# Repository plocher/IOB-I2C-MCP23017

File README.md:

# IOB-I2C-MCP23017
## License: CERN Open Hardware Licence v1.2

IOB I2C MCP23017 based IO Expander

The MCP23017 expander is an inexpensive and reliable device that supports up to 8x instances on a single I2C chain.

### Specifications

Each board provides a latched set of 16x IO points, with each point
being software selectable to be either an input or an output. The
individual points are reasonably protected from the environment, and can
source or sink 20 mA each (25mA absolute max).

### Communication Protocol

```C++
    enum MCP23017Registers {
        MCP23017_IODIRA   = 0x00,
        MCP23017_IODIRB   = 0x01,
        MCP23017_IPOLA    = 0x02,
        MCP23017_IPOLB    = 0x03,
        MCP23017_GPINTENA = 0x04,
        MCP23017_GPINTENB = 0x05,
        MCP23017_DEFVALA  = 0x06,
        MCP23017_DEFVALB  = 0x07,
        MCP23017_INTCONA  = 0x08,
        MCP23017_INTCONB  = 0x09,
        MCP23017_IOCONA   = 0x0A,
        MCP23017_IOCONB   = 0x0B,
        MCP23017_GPPUA    = 0x0C,
        MCP23017_GPPUB    = 0x0D,
        MCP23017_INTFA    = 0x0E,
        MCP23017_INTFB    = 0x0F,
        MCP23017_INTCAPA  = 0x10,
        MCP23017_INTCAPB  = 0x11,
        MCP23017_GPIOA    = 0x12,
        MCP23017_GPIOB    = 0x13,
        MCP23017_OLATA    = 0x14,
        MCP23017_OLATB    = 0x15,
    };

void I2Cexpander::init23017(uint8_t i2caddr, uint16_t dir) {
    if (i2caddr < base23017) {
        _i2c_address = base23017 + i2caddr;
    } else {
        _i2c_address = i2caddr;
    }
    Wire.beginTransmission(_i2c_address);
    Wire.write(MCP23017_IODIRA);
    Wire.write(0xff & dir);         // Low byte
    Wire.endTransmission();

    Wire.beginTransmission(_i2c_address);
    Wire.write(MCP23017_IODIRB);
    Wire.write(0xff & (dir >> 8));  // High byte
    Wire.endTransmission();

    // enable 100k pullups on all inputs...
    Wire.beginTransmission(_i2c_address);
    Wire.write(MCP23017_GPPUA);
    Wire.write(0xff & dir);         // Low byte
    Wire.endTransmission();

    Wire.beginTransmission(_i2c_address);
    Wire.write(MCP23017_GPPUB);
    Wire.write(0xff & (dir >> 8));  // High byte
    Wire.endTransmission();
}

uint32_t I2Cexpander::read23017() {
    uint32_t data = 0;
    Wire.beginTransmission(_i2c_address);
    Wire.write(MCP23017_GPIOA);
    Wire.endTransmission();

    Wire.requestFrom(_i2c_address, (uint8_t)2, (uint8_t)1);
    data = Wire.read();
    data |= (Wire.read() << 8);
    return data;
}

void I2Cexpander::write23017(uint32_t data) {
    data = data | _config;
    Wire.beginTransmission(_i2c_address);
    Wire.write(MCP23017_GPIOA);
    Wire.write(0xff & data);  //  low byte
    Wire.write(data >> 8);    //  high byte
    Wire.endTransmission();
}
```

See [I2Cexpander-lib](/pages/I2Cexpander "wikilink") for a more complete interface
library.

### Addressing
The addres selection for the MCP23017 is simple - set the desired address (in binary) on the 3x address selection switches.

**AD2**|**AD1**|**AD0**|**A6**|**A5**|**A4**|**A3**|**A2**|**A1**|**A0**|**ADDRESS (HEX)**
:-----:|:-----:|:-----:|:-----:|:-----:|:-----:|:-----:|:-----:|:-----:|:-----:|:-----:
GND|GND|GND|0|1|0|0|0|0|0|0x20
GND|GND|V+|0|1|0|0|0|0|1|0x21
GND|V+|GND|0|1|0|0|0|1|0|0x22
GND|V+|V+|0|1|0|0|0|1|1|0x23
V+|GND|GND|0|1|0|0|1|0|0|0x24
V+|GND|V+|0|1|0|0|1|0|1|0x25
V+|V+|GND|0|1|0|0|1|1|0|0x26
V+|V+|V+|0|1|0|0|1|1|1|0x27

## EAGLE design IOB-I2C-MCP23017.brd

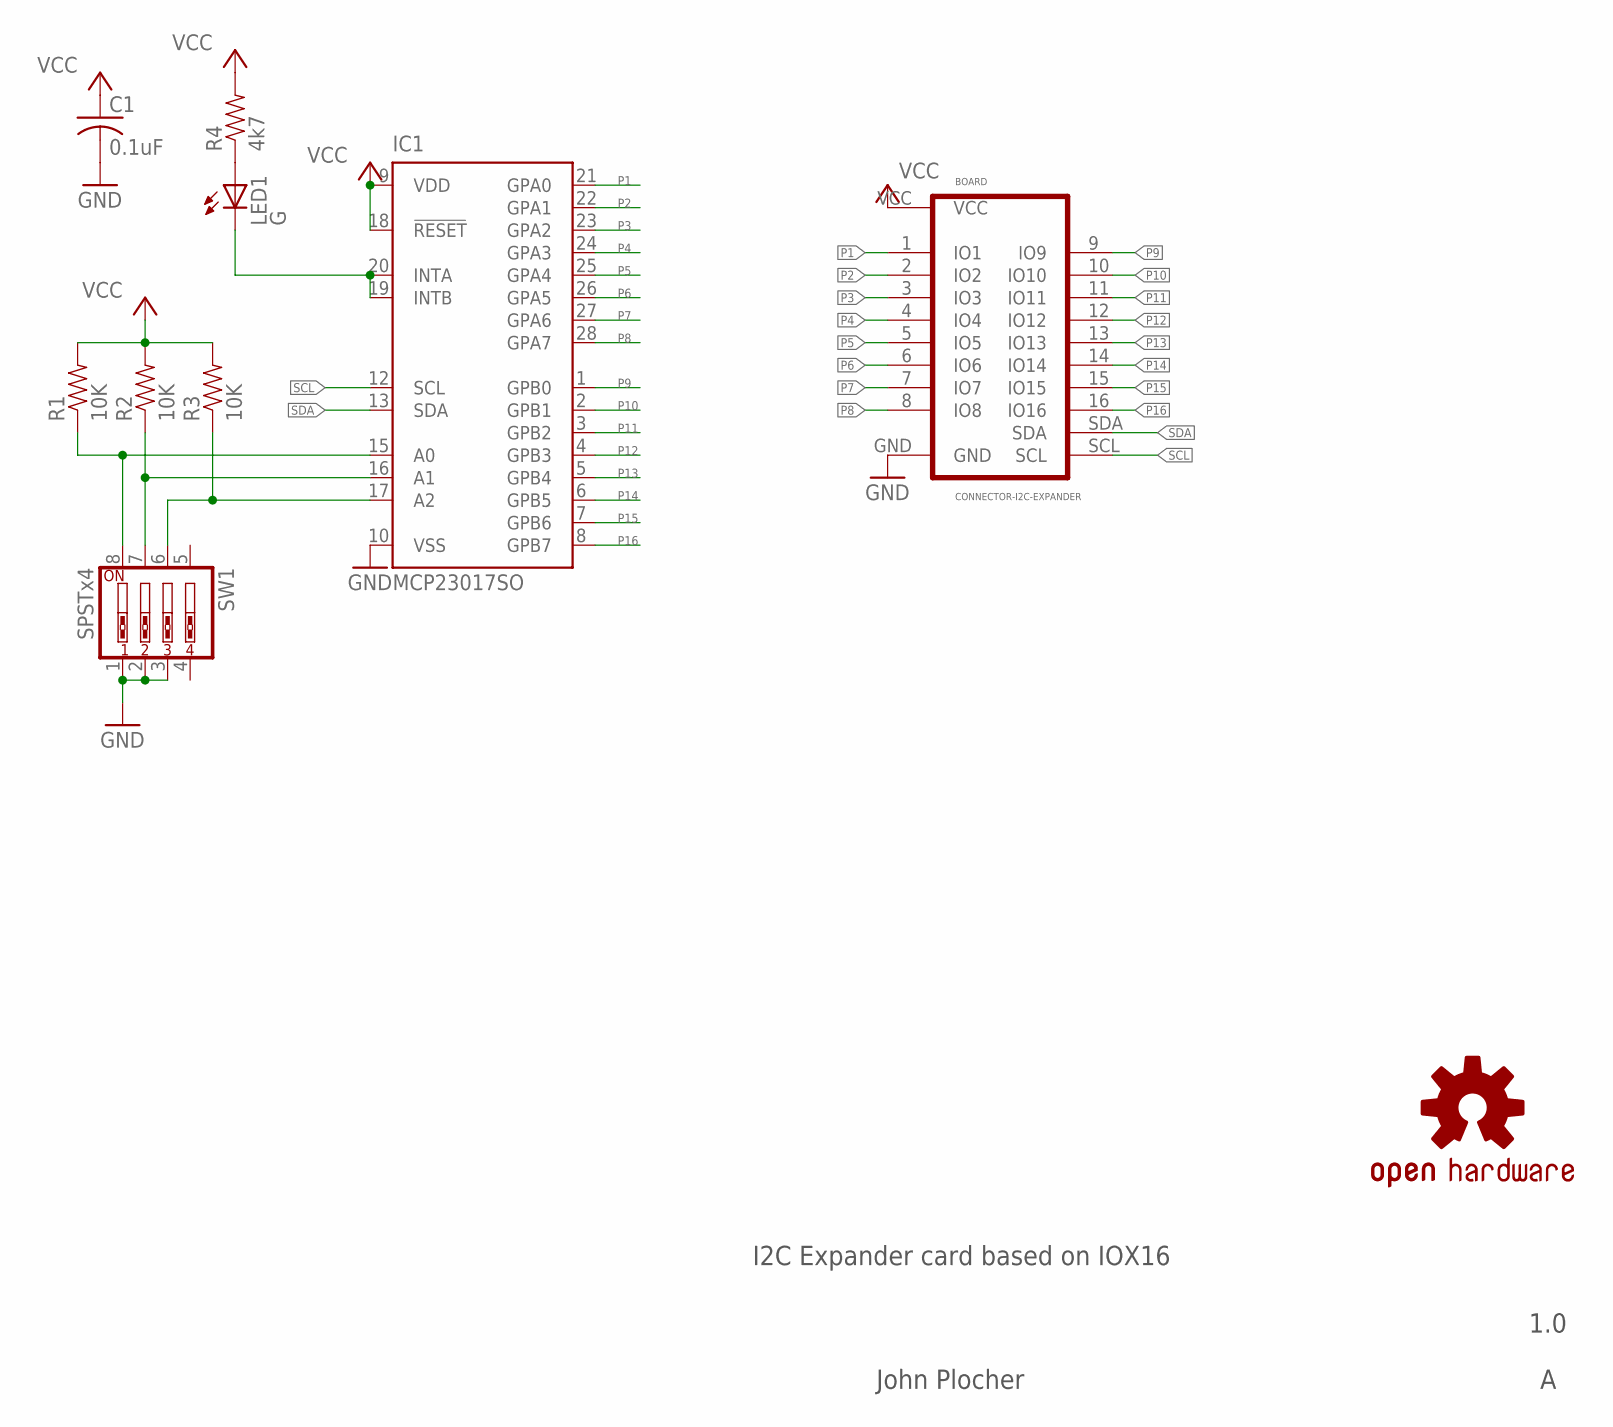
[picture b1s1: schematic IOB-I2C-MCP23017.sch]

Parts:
BOARD: CONNECTOR-I2C-EXPANDER; I2C-EXPANDER
C1: 0.1uF; 0603-CAP
IC1: MCP23017SO; SO28W
LED1: G; 0603-LED
OSHW1: OSHW; OSHW-LOGO-M
R1, R2, R3: 10K; 0603-RES
R4: 4k7; 0603-RES
SW1: SPSTx4; EDG-04

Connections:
A0: IC1.15 (A0), R1.1, SW1.8
A1: IC1.16 (A1), R2.1, SW1.7
A3: IC1.17 (A2), R3.1, SW1.6
GND: BOARD.GND, C1.2, IC1.10 (VSS), SW1.1, SW1.2, SW1.3
unnamed: LED1.A, R4.1
unnamed: IC1.19 (INTB), IC1.20 (INTA), LED1.C
P1: BOARD.1 (IO1), IC1.21 (GPA0)
P2: BOARD.2 (IO2), IC1.22 (GPA1)
P3: BOARD.3 (IO3), IC1.23 (GPA2)
P4: BOARD.4 (IO4), IC1.24 (GPA3)
P5: BOARD.5 (IO5), IC1.25 (GPA4)
P6: BOARD.6 (IO6), IC1.26 (GPA5)
P7: BOARD.7 (IO7), IC1.27 (GPA6)
P8: BOARD.8 (IO8), IC1.28 (GPA7)
P9: BOARD.9 (IO9), IC1.1 (GPB0)
P10: BOARD.10 (IO10), IC1.2 (GPB1)
P11: BOARD.11 (IO11), IC1.3 (GPB2)
P12: BOARD.12 (IO12), IC1.4 (GPB3)
P13: BOARD.13 (IO13), IC1.5 (GPB4)
P14: BOARD.14 (IO14), IC1.6 (GPB5)
P15: BOARD.15 (IO15), IC1.7 (GPB6)
P16: BOARD.16 (IO16), IC1.8 (GPB7)
SCL: BOARD.SCL, IC1.12 (SCL)
SDA: BOARD.SDA, IC1.13 (SDA)
VCC: BOARD.VCC, C1.1, IC1.9 (VDD), IC1.18 (!RESET), R1.2, R2.2, R3.2, R4.2

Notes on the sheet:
I2C Expander card based on IOX16
1.0
John Plocher

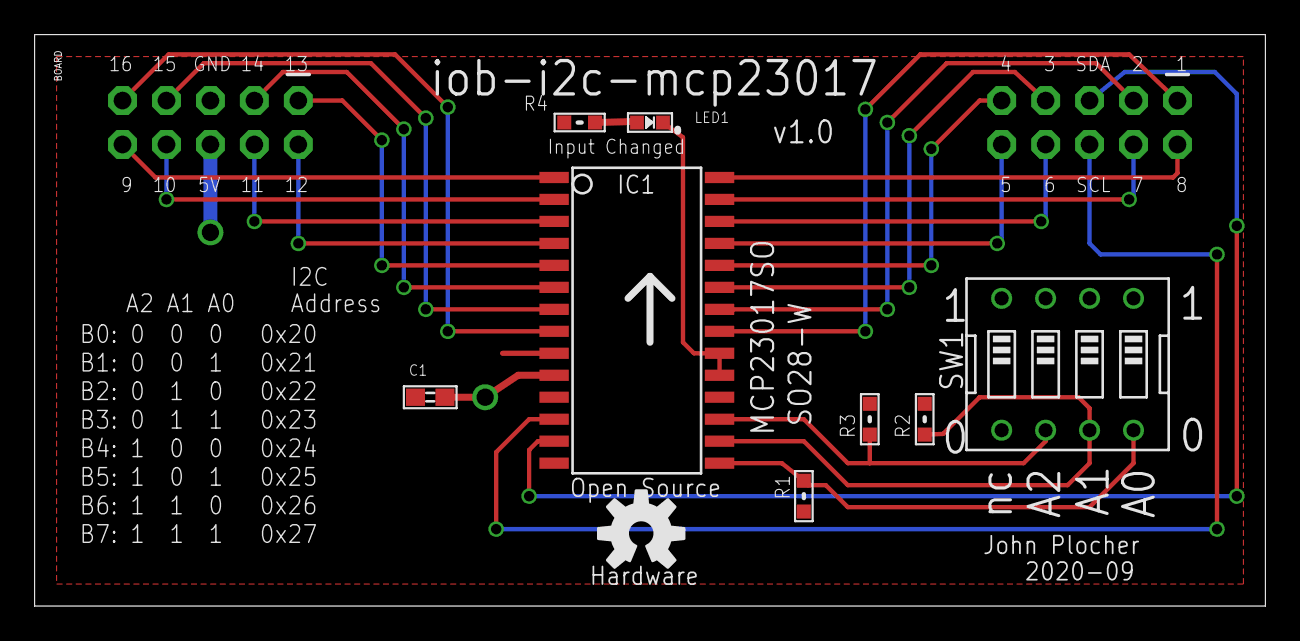
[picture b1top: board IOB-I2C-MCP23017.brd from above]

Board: 2 copper layers, 71.1 x 33.0 mm, 10 parts (0 on the bottom side), 25 nets.

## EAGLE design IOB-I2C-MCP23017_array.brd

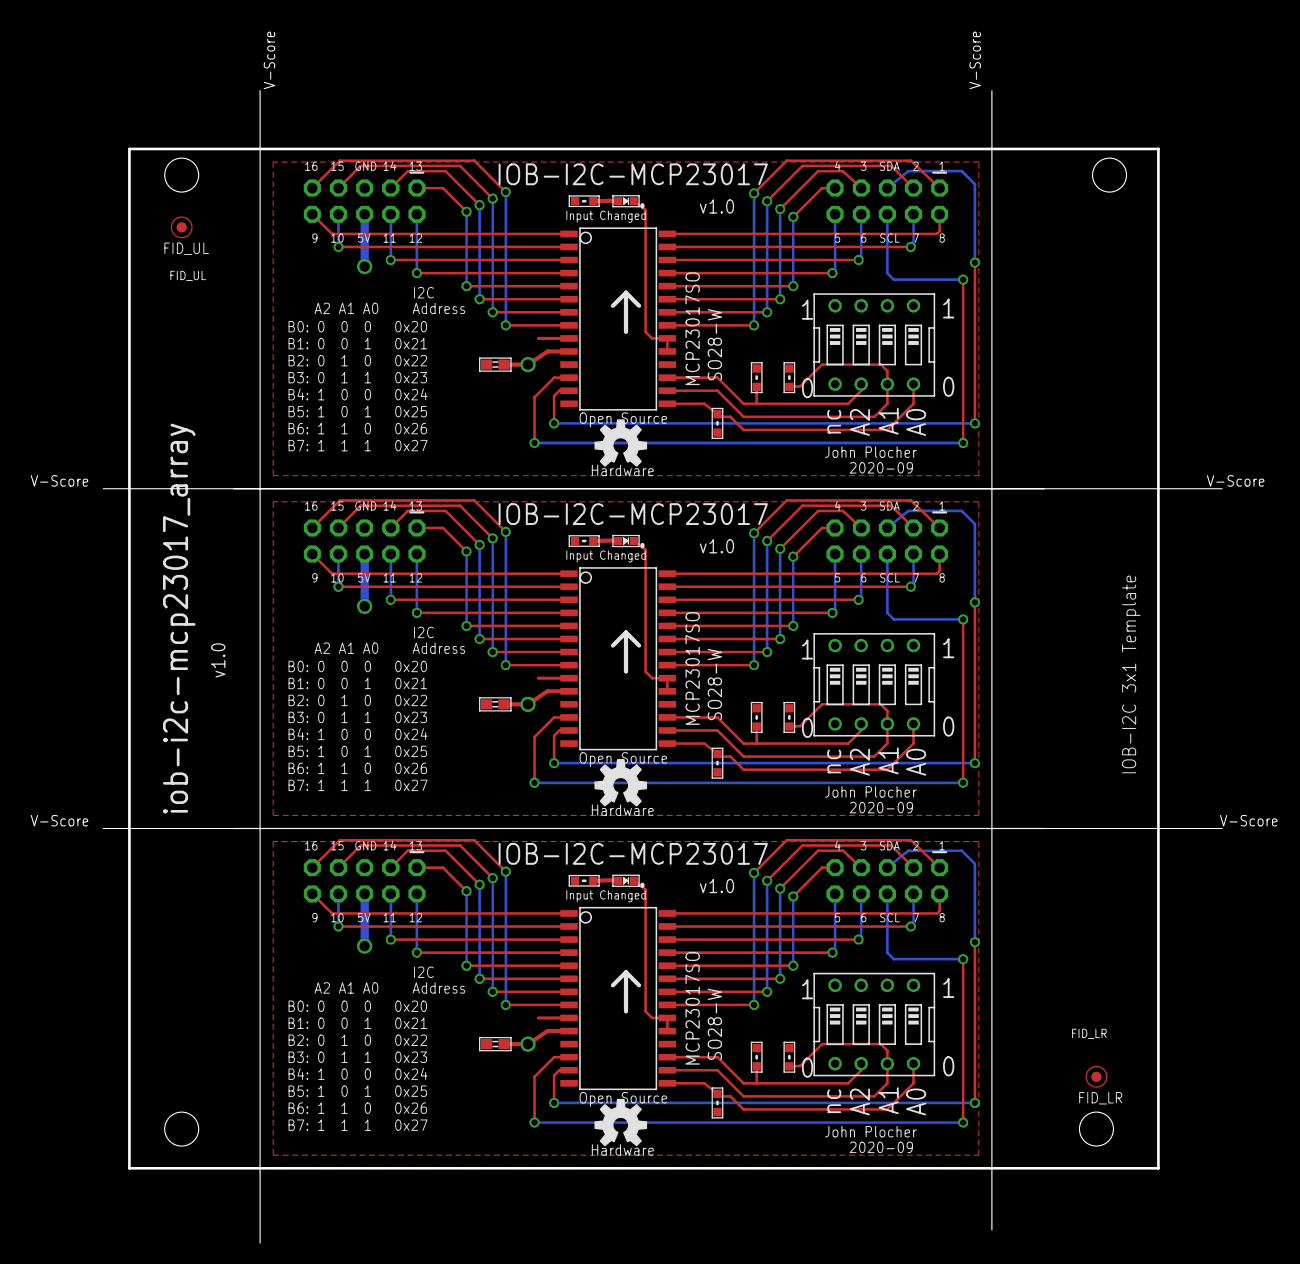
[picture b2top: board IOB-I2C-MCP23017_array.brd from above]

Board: 2 copper layers, 122.1 x 118.6 mm, 33 parts (0 on the bottom side), 75 nets.

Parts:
BOARDX11, BOARDX12, BOARDX13: CONNECTOR-I2C-EXPANDER; I2C-EXPANDER
C1X11, C1X12, C1X13: 0.1uF; 0603-CAP
FID_LR: FIDUCIAL; FIDUCIAL_1MM
FID_UL: FIDUCIAL; FIDUCIAL_1MM
IC1X11, IC1X12, IC1X13: MCP23017SO; SO28W
LED1X11, LED1X12, LED1X13: G; 0603-LED
OSHW1X11, OSHW1X12, OSHW1X13: DOC-OSHW-LOGO-M; OSHW-LOGO-M
R1X11, R1X12, R1X13, R2X11, R2X12, R2X13, R3X11, R3X12, R3X13: 10K; 0603-RES
R4X11, R4X12, R4X13: 4k7; 0603-RES
SW1X11, SW1X12, SW1X13: SPSTx4; EDG-04
U$5X1: BOARD; BOARD-TEMPLATE-IOB-I2C-3X1-ARRAY

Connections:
A0X11: IC1X11.15, R1X11.1, SW1X11.8
A0X12: IC1X12.15, R1X12.1, SW1X12.8
A0X13: IC1X13.15, R1X13.1, SW1X13.8
A1X11: IC1X11.16, R2X11.1, SW1X11.7
A1X12: IC1X12.16, R2X12.1, SW1X12.7
A1X13: IC1X13.16, R2X13.1, SW1X13.7
A3X11: IC1X11.17, R3X11.1, SW1X11.6
A3X12: IC1X12.17, R3X12.1, SW1X12.6
A3X13: IC1X13.17, R3X13.1, SW1X13.6
GNDX11: BOARDX11.GND, C1X11.2, IC1X11.10, SW1X11.1, SW1X11.2, SW1X11.3
GNDX12: BOARDX12.GND, C1X12.2, IC1X12.10, SW1X12.1, SW1X12.2, SW1X12.3
GNDX13: BOARDX13.GND, C1X13.2, IC1X13.10, SW1X13.1, SW1X13.2, SW1X13.3
unnamed: LED1X11.A, R4X11.1
unnamed: LED1X12.A, R4X12.1
unnamed: LED1X13.A, R4X13.1
unnamed: IC1X11.19, IC1X11.20, LED1X11.C
unnamed: IC1X12.19, IC1X12.20, LED1X12.C
unnamed: IC1X13.19, IC1X13.20, LED1X13.C
P1X11: BOARDX11.1, IC1X11.21
P1X12: BOARDX12.1, IC1X12.21
P1X13: BOARDX13.1, IC1X13.21
P2X11: BOARDX11.2, IC1X11.22
P2X12: BOARDX12.2, IC1X12.22
P2X13: BOARDX13.2, IC1X13.22
P3X11: BOARDX11.3, IC1X11.23
P3X12: BOARDX12.3, IC1X12.23
P3X13: BOARDX13.3, IC1X13.23
P4X11: BOARDX11.4, IC1X11.24
P4X12: BOARDX12.4, IC1X12.24
P4X13: BOARDX13.4, IC1X13.24
P5X11: BOARDX11.5, IC1X11.25
P5X12: BOARDX12.5, IC1X12.25
P5X13: BOARDX13.5, IC1X13.25
P6X11: BOARDX11.6, IC1X11.26
P6X12: BOARDX12.6, IC1X12.26
P6X13: BOARDX13.6, IC1X13.26
P7X11: BOARDX11.7, IC1X11.27
P7X12: BOARDX12.7, IC1X12.27
P7X13: BOARDX13.7, IC1X13.27
P8X11: BOARDX11.8, IC1X11.28
P8X12: BOARDX12.8, IC1X12.28
P8X13: BOARDX13.8, IC1X13.28
P9X11: BOARDX11.9, IC1X11.1
P9X12: BOARDX12.9, IC1X12.1
P9X13: BOARDX13.9, IC1X13.1
P10X11: BOARDX11.10, IC1X11.2
P10X12: BOARDX12.10, IC1X12.2
P10X13: BOARDX13.10, IC1X13.2
P11X11: BOARDX11.11, IC1X11.3
P11X12: BOARDX12.11, IC1X12.3
P11X13: BOARDX13.11, IC1X13.3
P12X11: BOARDX11.12, IC1X11.4
P12X12: BOARDX12.12, IC1X12.4
P12X13: BOARDX13.12, IC1X13.4
P13X11: BOARDX11.13, IC1X11.5
P13X12: BOARDX12.13, IC1X12.5
P13X13: BOARDX13.13, IC1X13.5
P14X11: BOARDX11.14, IC1X11.6
P14X12: BOARDX12.14, IC1X12.6
P14X13: BOARDX13.14, IC1X13.6
P15X11: BOARDX11.15, IC1X11.7
P15X12: BOARDX12.15, IC1X12.7
P15X13: BOARDX13.15, IC1X13.7
P16X11: BOARDX11.16, IC1X11.8
P16X12: BOARDX12.16, IC1X12.8
P16X13: BOARDX13.16, IC1X13.8
SCLX11: BOARDX11.SCL, IC1X11.12
SCLX12: BOARDX12.SCL, IC1X12.12
SCLX13: BOARDX13.SCL, IC1X13.12
SDAX11: BOARDX11.SDA, IC1X11.13
SDAX12: BOARDX12.SDA, IC1X12.13
SDAX13: BOARDX13.SDA, IC1X13.13
VCCX11: BOARDX11.VCC, C1X11.1, IC1X11.9, IC1X11.18, R1X11.2, R2X11.2, R3X11.2, R4X11.2
VCCX12: BOARDX12.VCC, C1X12.1, IC1X12.9, IC1X12.18, R1X12.2, R2X12.2, R3X12.2, R4X12.2
VCCX13: BOARDX13.VCC, C1X13.1, IC1X13.9, IC1X13.18, R1X13.2, R2X13.2, R3X13.2, R4X13.2

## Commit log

2020-09-04 Initial version
2020-09-05 added graphic
2020-09-05 cleanup
2020-09-11 cleanup layout
2020-09-11 update docs
2020-10-05 added values for connectors
2020-10-05 added missing values
2020-10-06 normalized values

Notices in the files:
parts and their libraries:
SPCoast: http://freedomdefined.org/OSHW Creative Commons - Attribution - ShareAlike 3.0
